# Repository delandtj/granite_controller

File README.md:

# granite

The Granite immersion frame electronics: the 48 V power plane, the
plane-core firmware, the controller and the software shared between them.

granite_controller and granite-plane merged on 2026-10-30. granite-plane
was split from granite_controller on 2026-10-29; its commits were replayed
on top of granite_controller's history, so both histories are here.

## Layout

- controller-fd: the controller with the CAN FD plane link (ADR 0006),
  the live design. tools/fd_build.sh builds it from the rev D board in
  attic/controller-rev-d.
- controller-rev-c: the rev C controller board (relays, expanders, 19 V
  input), kept as demoware. Tag rev-c-demo is the last rev C state of
  the whole repo, firmware included.
- power/pp-48-fd: plane tools and libraries for the CAN FD link
  (ADR 0006). power/pp-48-core-fd, power/pp-48-unit-fd: the chained plane
  (ADR 0005), one core board and identical 2-slot unit boards.
- power/pp-48: the I2C-link plane tools (schematic generator, placement
  and routing scripts), pp.kicad_sym, pp48.pretty, pp48.3dshapes; its
  schematic engine is also used by pm-19v-250w-b, and the attic boards
  use its libraries.
- power/pm-19v-250w, power/pm-19v-250w-b: the port module. power/pm-bench-carrier: bench
  carrier for one module. power/tools: module mount geometry.
- mech: the mechanical side. mech/frame: the 3D-printed pod frames
  (node, infra and end frame, plane carrier), FreeCAD models and
  freecadcmd generators; mech/pod-layout: the pod layout page;
  mech/halo-clamp: the Strix Halo cooler bridge; mech/assembly: the
  8-port plane assembly. Handoff in docs/handoff-frames.md. Moved in
  from ~/Granite/Hardware on 2026-11-26.
- site: installer / operator manual (mdBook). Still describes rev C
  (relays, expanders, 19 V input); to be reworked for rev D and the plane.
- firmware: Rust workspace. granite-core (no_std: dispatcher, commands,
  MQTT / HTTP / Modbus surfaces, rules, config), granite-sim (host
  simulator), granite-fw (ESP32-C6 binary, still the rev C hardware
  layer), web UI.
- docs: ADRs 0001-0007, plane requirements, module interface, controller
  specs, handoff. Firmware ADRs in firmware/docs/adr.
- attic: superseded designs, kept for reference, not maintained.
  - attic/power/pp-48-2s: the first 2-slot plane (ADR 0001 / 0002).
  - attic/power/pm-19v-200w: the first port module (obsolete since
    2026-10-27, replaced by pm-19v-250w).
  - attic/power/pp-48-rev1: the single-board plane (ADR 0004, tag
    pp48-rev1); uses the libraries in power/pp-48.
  - attic/controller-rev-d: the I2C-link controller (rev D), superseded
    by controller-fd (2026-11-10); still the input board of
    controller-fd/tools/fd_build.sh.
  - attic/power/pp-48-core, attic/power/pp-48-unit: the I2C-link chained
    plane (ADR 0005), superseded by the -fd boards (2026-11-10); still the
    input boards of power/pp-48-fd/tools/fd_layout.sh and the output of
    power/pp-48/tools/gensch.py.
  - attic/firmware/plane-fw, attic/firmware/plane-core-pins.toml: the
    rev D plane binary (I2C link) and its pin map, frozen 2026-11-10;
    builds against firmware/granite-proto and firmware/plane-logic. The
    FD plane binary is firmware/plane-fd (firmware ADR 0005 decision 9).
  Older docs and the handoff name these at their old paths
  (power/pp-48-2s, power/pm-19v-200w, power/pp-48/pp-48.kicad_*,
  controller, power/pp-48-core, power/pp-48-unit).

## Direction (decided 2026-10-29)

- Plane core firmware on the STM32G070 (embassy), I2C slave to the
  controller, master to the units through the TCA9548A.
- Plane firmware updated from the controller over the link: own A/B
  bootloader (embassy-boot) that keeps the plane's strapped address,
  rollback on a failed self-test. ST's ROM bootloader only as a bench
  recovery path.
- The plane core owns node sequencing (press deadlines, power-cycle,
  retry / latch policy, stagger); the controller does policy, rules and
  the network.
- One controller serves several planes over isolated I2C (ISO1640 +
  EXP_INT, daisy chain, plane addresses 0x30-0x37).
- One TLV protocol crate used by the plane firmware, the controller and
  the simulator.
- Controller rev D: rev C minus the relays, expanders, LED sense and
  19 V input; 12 V from the plane's isolated aux.

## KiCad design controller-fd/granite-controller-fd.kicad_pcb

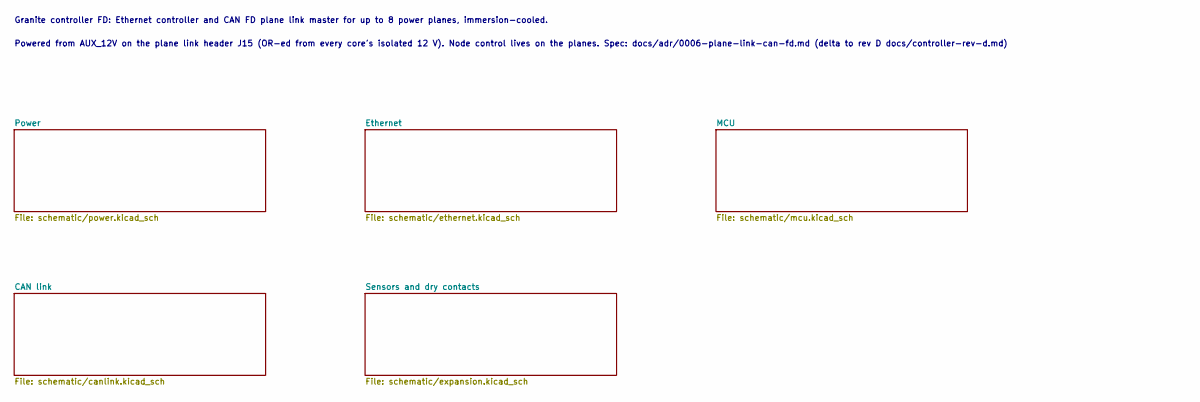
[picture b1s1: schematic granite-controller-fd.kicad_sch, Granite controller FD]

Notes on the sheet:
Granite controller FD: Ethernet controller and CAN FD plane link master for up to 8 power planes, immersion-cooled.
Powered from AUX_12V on the plane link header J15 (OR-ed from every core's isolated 12 V). Node control lives on the planes. Spec: docs/adr/0006-plane-link-can-fd.md (delta to rev D docs/controller-rev-d.md)

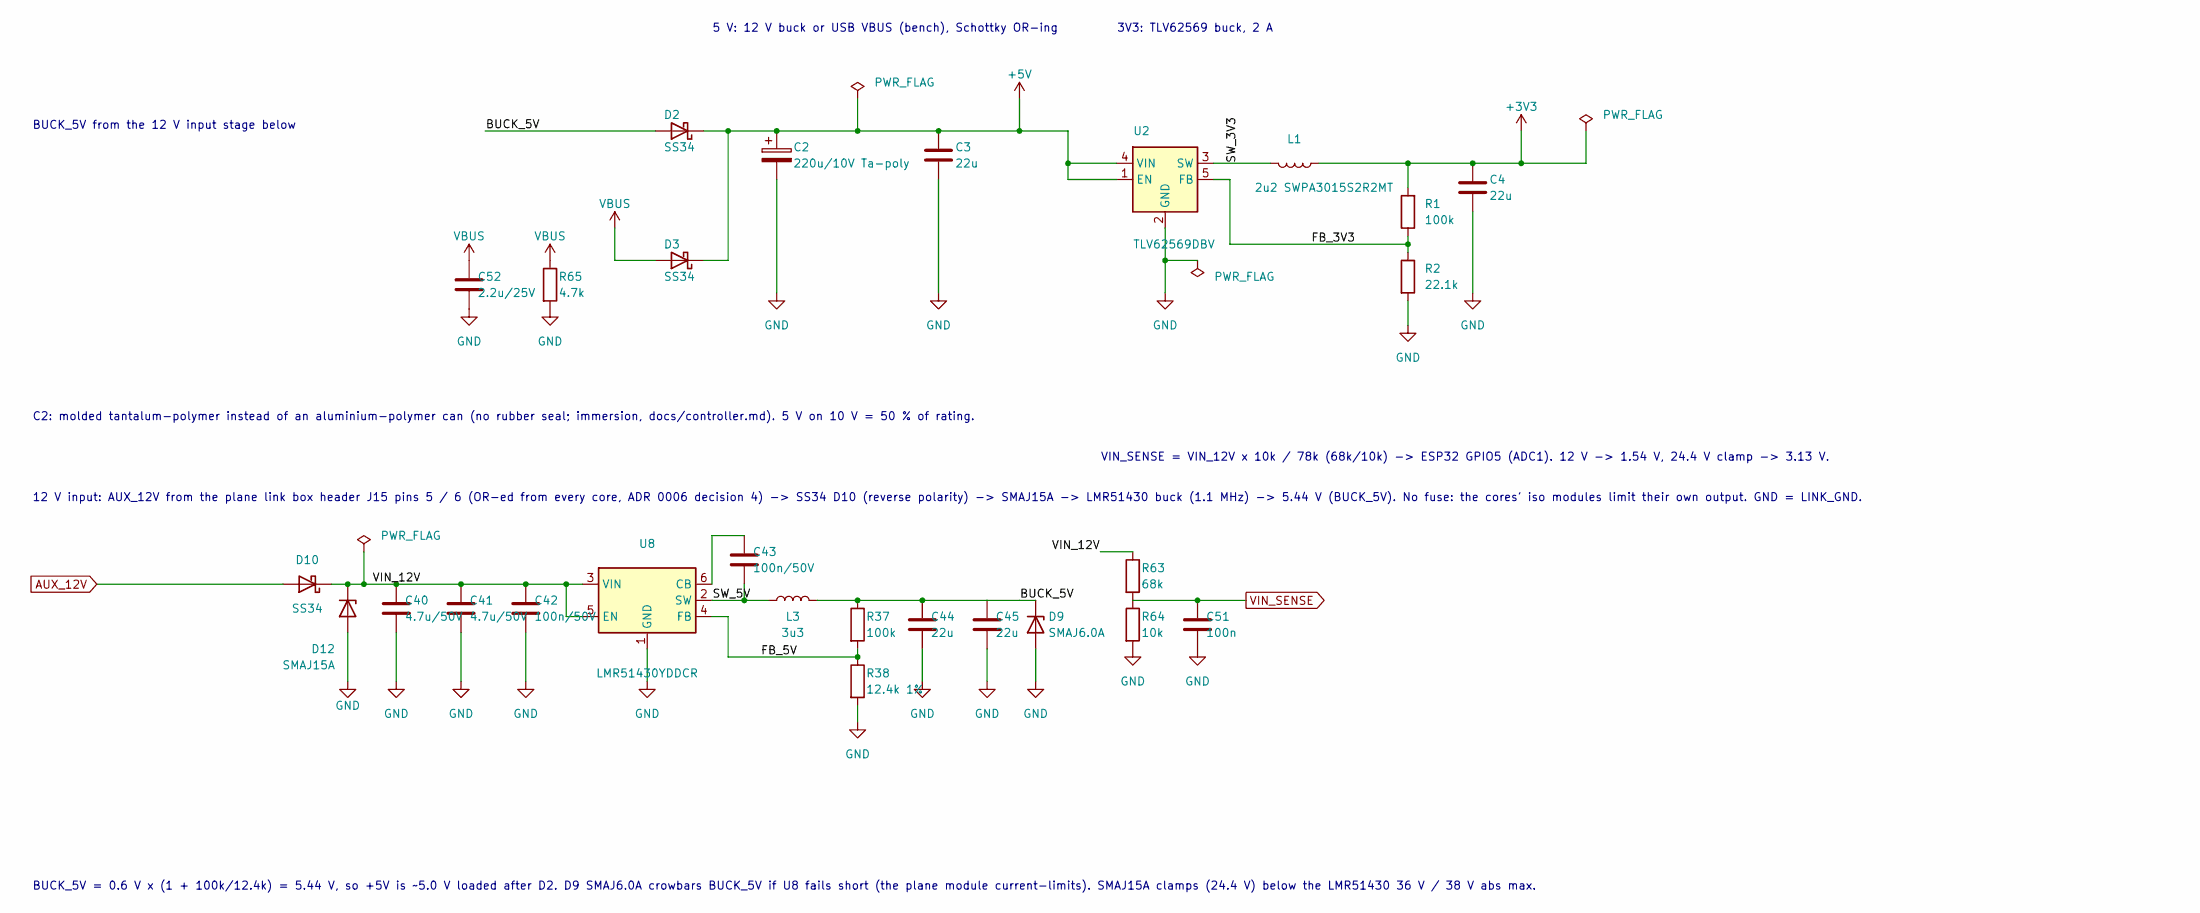
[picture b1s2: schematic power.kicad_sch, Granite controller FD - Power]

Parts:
C2: 220u/10V Ta-poly; CP_EIA-7343-31_Kemet-D; MPN T520D227M010ATE018; LCSC C116742
C3, C4, C44, C45: 22u; C_0805_2012Metric; MPN CL21A226MAQNNNE; LCSC C45783
C40, C41: 4.7u/50V; C_1206_3216Metric; MPN 1206B475K500NT; LCSC C29823
C42, C43: 100n/50V; C_0402_1005Metric; MPN CL05B104KB54PNC; LCSC C307331
C51: 100n; C_0402_1005Metric; MPN CL05B104KO5NNNC; LCSC C1525
C52: 2.2u/25V; C_0603_1608Metric; MPN CL10A225KA8NNNC; LCSC C57895
D2, D3, D10: SS34; D_SMA; MPN SS34; LCSC C8678
D9: SMAJ6.0A; D_SMA; MPN SMAJ6.0A; LCSC C364284
D12: SMAJ15A; D_SMA; MPN SMAJ15A; LCSC C148216
L1: 2u2 SWPA3015S2R2MT; L_Sunlord_SWPA3015S; MPN SWPA3015S2R2MT; LCSC C43389
L3: 3u3; L_Changjiang_FXL0630; MPN FXL0630-3R3-M; LCSC C167219
R1, R37: 100k; R_0402_1005Metric; MPN 0402WGF1003TCE; LCSC C25741
R2: 22.1k; R_0402_1005Metric; MPN RC0402FR-0722K1L; LCSC C163478
R38: 12.4k 1%; R_0402_1005Metric; MPN 0402WGF1242TCE; LCSC C11692
R63: 68k; R_0402_1005Metric; MPN 0402WGF6802TCE; LCSC C36871
R64: 10k; R_0402_1005Metric; MPN 0402WGF1002TCE; LCSC C25744
R65: 4.7k; R_0402_1005Metric; MPN 0402WGF4701TCE; LCSC C25900
U2: TLV62569DBV; SOT-23-5; MPN TLV62569DBVR; LCSC C141836
U8: LMR51430YDDCR; SOT-23-6; MPN LMR51430YDDCR; LCSC C5210749

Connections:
+3V3: C4.1, L1.1, R1.2; also elsewhere on the board
+5V: C2.1, C3.1, D2.1 (K), D3.1 (K), U2.1 (EN), U2.4 (VIN); also elsewhere on the board
/Power/BUCK_5V: C44.1, C45.1, D2.2 (A), D9.1 (K), L3.2, R37.1
/Power/FB_3V3: R1.1, R2.1, U2.5 (FB)
/Power/FB_5V: R37.2, R38.1, U8.4 (FB)
/Power/SW_3V3: L1.2, U2.3 (SW)
/Power/SW_5V: C43.2, L3.1, U8.2 (SW)
/Power/VIN_12V: C40.1, C41.1, C42.1, D10.1 (K), D12.1 (K), R63.1, U8.3 (VIN), U8.5 (EN)
AUX_12V: D10.2 (A); also elsewhere on the board
GND: C2.2, C3.2, C4.2, C40.2, C41.2, C42.2, C44.2, C45.2, C51.2, C52.2, D9.2 (A), D12.2 (A), R2.2, R38.2, R64.2, R65.2, U2.2 (GND), U8.1 (GND); also elsewhere on the board
unnamed: C43.1, U8.6 (CB)
VBUS: C52.1, D3.2 (A), R65.1; also elsewhere on the board
VIN_SENSE: C51.1, R63.2, R64.1; also elsewhere on the board

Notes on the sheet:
5 V: 12 V buck or USB VBUS (bench), Schottky OR-ing
3V3: TLV62569 buck, 2 A
BUCK_5V from the 12 V input stage below
12 V input: AUX_12V from the plane link box header J15 pins 5 / 6 (OR-ed from every core, ADR 0006 decision 4) -> SS34 D10 (reverse polarity) -> SMAJ15A -> LMR51430 buck (1.1 MHz) -> 5.44 V (BUCK_5V). No fuse: the cores' iso modules limit their own output. GND = LINK_GND.
BUCK_5V = 0.6 V x (1 + 100k/12.4k) = 5.44 V, so +5V is ~5.0 V loaded after D2. D9 SMAJ6.0A crowbars BUCK_5V if U8 fails short (the plane module current-limits). SMAJ15A clamps (24.4 V) below the LMR51430 36 V / 38 V abs max.
C2: molded tantalum-polymer instead of an aluminium-polymer can (no rubber seal; immersion, docs/controller.md). 5 V on 10 V = 50 % of rating.
VIN_SENSE = VIN_12V x 10k / 78k (68k/10k) -> ESP32 GPIO5 (ADC1). 12 V -> 1.54 V, 24.4 V clamp -> 3.13 V.

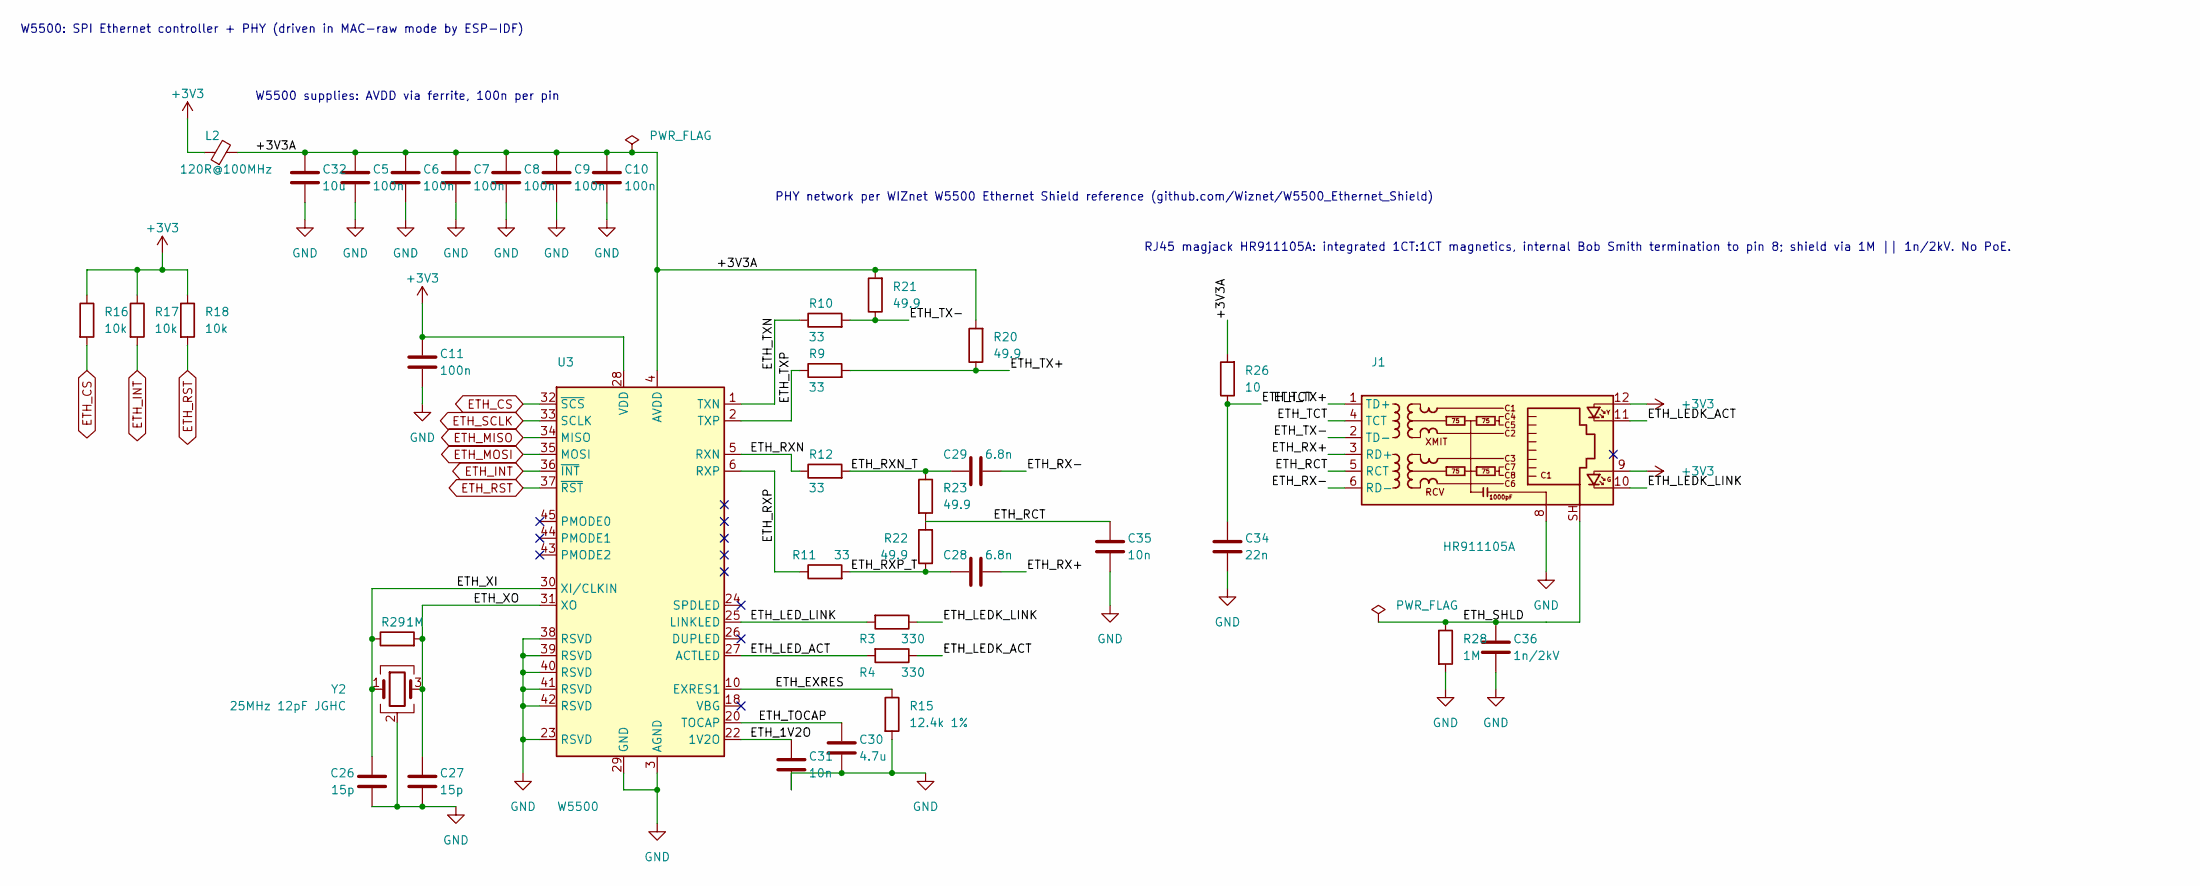
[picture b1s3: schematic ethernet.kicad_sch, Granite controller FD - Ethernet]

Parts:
C5, C6, C7, C8, C9, C10, C11: 100n; C_0402_1005Metric; MPN CL05B104KO5NNNC; LCSC C1525
C26, C27: 15p; C_0402_1005Metric; MPN 0402CG150J500NT; LCSC C1548
C28, C29: 6.8n; C_0402_1005Metric; MPN CC0402KRX7R9BB682; LCSC C93654
C30: 4.7u; C_0603_1608Metric; MPN CL10A475KO8NNNC; LCSC C19666
C31, C35: 10n; C_0402_1005Metric; MPN CL05B103KB5NNNC; LCSC C15195
C32: 10u; C_0805_2012Metric; MPN CL21A106KAYNNNE; LCSC C15850
C34: 22n; C_0402_1005Metric; MPN 0402B223K500NT; LCSC C1532
C36: 1n/2kV; C_1812_4532Metric; MPN CC1812KKX7RDBB102; LCSC C118019
J1: HR911105A; RJ45_Hanrun_HR911105A_Horizontal; MPN HR911105A; LCSC C12074
L2: 120R@100MHz; L_0603_1608Metric; MPN BLM18PG121SN1D; LCSC C14709
R3, R4: 330; R_0402_1005Metric; MPN 0402WGF3300TCE; LCSC C25104
R9, R10, R11, R12: 33; R_0402_1005Metric; MPN 0402WGF330JTCE; LCSC C25105
R15: 12.4k 1%; R_0402_1005Metric; MPN 0402WGF1242TCE; LCSC C11692
R16, R17, R18: 10k; R_0402_1005Metric; MPN 0402WGF1002TCE; LCSC C25744
R20, R21, R22, R23: 49.9; R_0402_1005Metric; MPN 0402WGF499JTCE; LCSC C25120
R26: 10; R_0402_1005Metric; MPN 0402WGF100JTCE; LCSC C25077
R28: 1M; R_0603_1608Metric; MPN 0603WAF1004T5E; LCSC C22935
R29: 1M; R_0402_1005Metric; MPN 0402WGF1004TCE; LCSC C26083
U3: W5500; LQFP-48_7x7mm_P0.5mm; MPN W5500; LCSC C32843
Y2: 25MHz 12pF JGHC; Crystal_SMD_Abracon_ABM8G-4Pin_3.2x2.5mm; MPN S3225000121060; LCSC C390773

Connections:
+3V3: C11.1, J1.9, J1.12, L2.1, R16.1, R17.1, R18.1, U3.28 (VDD); also elsewhere on the board
/Ethernet/+3V3A: C5.1, C6.1, C7.1, C8.1, C9.1, C10.1, C32.1, L2.2, R20.2, R21.2, R26.2, U3.4 (AVDD), U3.8 (AVDD), U3.11 (AVDD), U3.15 (AVDD), U3.17 (AVDD), U3.21 (AVDD)
/Ethernet/ETH_1V2O: C31.1, U3.22 (1V2O)
/Ethernet/ETH_EXRES: R15.1, U3.10 (EXRES1)
/Ethernet/ETH_LEDK_ACT: J1.11, R4.1
/Ethernet/ETH_LEDK_LINK: J1.10, R3.1
/Ethernet/ETH_LED_ACT: R4.2, U3.27 (ACTLED)
/Ethernet/ETH_LED_LINK: R3.2, U3.25 (LINKLED)
/Ethernet/ETH_RCT: C35.1, J1.5 (RCT), R22.2, R23.2
/Ethernet/ETH_RX+: C28.2, J1.3 (RD+)
/Ethernet/ETH_RX-: C29.2, J1.6 (RD-)
/Ethernet/ETH_RXN: R12.1, U3.5 (RXN)
/Ethernet/ETH_RXN_T: C29.1, R12.2, R23.1
/Ethernet/ETH_RXP: R11.1, U3.6 (RXP)
/Ethernet/ETH_RXP_T: C28.1, R11.2, R22.1
/Ethernet/ETH_SHLD: C36.1, J1.SH, R28.1
/Ethernet/ETH_TCT: C34.1, J1.4 (TCT), R26.1
/Ethernet/ETH_TOCAP: C30.1, U3.20 (TOCAP)
/Ethernet/ETH_TX+: J1.1 (TD+), R9.2, R20.1
/Ethernet/ETH_TX-: J1.2 (TD-), R10.2, R21.1
/Ethernet/ETH_TXN: R10.1, U3.1 (TXN)
/Ethernet/ETH_TXP: R9.1, U3.2 (TXP)
/Ethernet/ETH_XI: C26.1, R29.1, U3.30 (XI/CLKIN), Y2.1
/Ethernet/ETH_XO: C27.1, R29.2, U3.31 (XO), Y2.3
ETH_CS: R16.2, U3.32 (~SCS); also elsewhere on the board
ETH_INT: R17.2, U3.36 (~INT); also elsewhere on the board
ETH_MISO: U3.34 (MISO); also elsewhere on the board
ETH_MOSI: U3.35 (MOSI); also elsewhere on the board
ETH_RST: R18.2, U3.37 (~RST); also elsewhere on the board
ETH_SCLK: U3.33 (SCLK); also elsewhere on the board
GND: C5.2, C6.2, C7.2, C8.2, C9.2, C10.2, C11.2, C26.2, C27.2, C30.2, C31.2, C32.2, C34.2, C35.2, C36.2, J1.8, R15.2, R28.2, U3.3 (AGND), U3.9 (AGND), U3.14 (AGND), U3.16 (AGND), U3.19 (AGND), U3.23 (RSVD), U3.29 (GND), U3.38 (RSVD), U3.39 (RSVD), U3.40 (RSVD), U3.41 (RSVD), U3.42 (RSVD), U3.48 (AGND), Y2.2 (G), Y2.4 (G); also elsewhere on the board

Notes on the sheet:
W5500: SPI Ethernet controller + PHY (driven in MAC-raw mode by ESP-IDF)
W5500 supplies: AVDD via ferrite, 100n per pin
PHY network per WIZnet W5500 Ethernet Shield reference (github.com/Wiznet/W5500_Ethernet_Shield)
RJ45 magjack HR911105A: integrated 1CT:1CT magnetics, internal Bob Smith termination to pin 8; shield via 1M || 1n/2kV. No PoE.

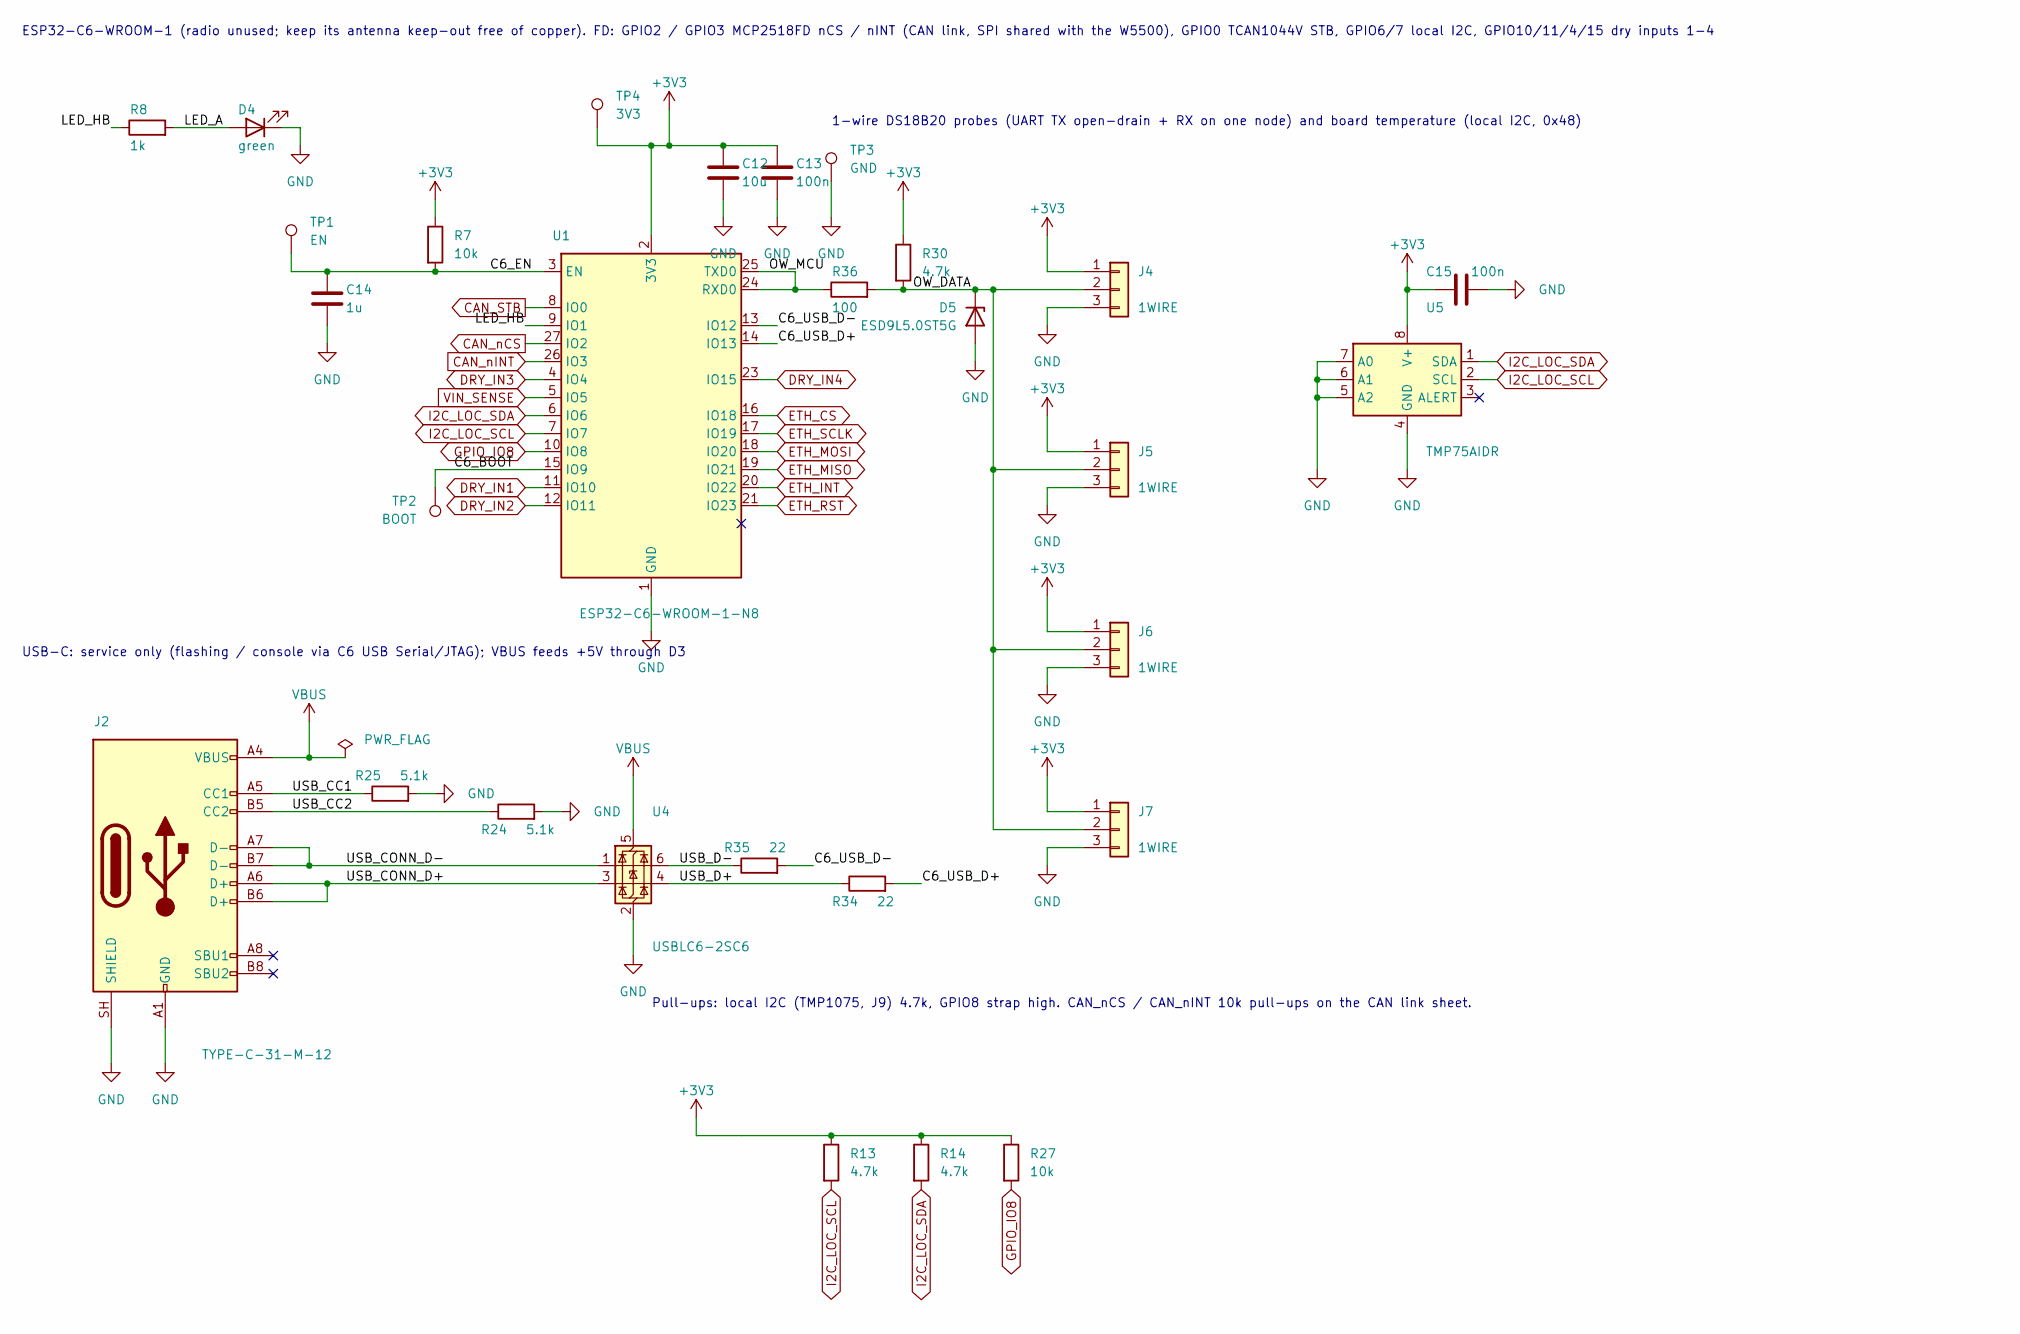
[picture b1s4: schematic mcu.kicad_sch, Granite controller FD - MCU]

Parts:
C12: 10u; C_0805_2012Metric; MPN CL21A106KAYNNNE; LCSC C15850
C13, C15: 100n; C_0402_1005Metric; MPN CL05B104KO5NNNC; LCSC C1525
C14: 1u; C_0603_1608Metric; MPN CL10A105KB8NNNC; LCSC C15849
D4: green; LED_0603_1608Metric; MPN KT-0603G; LCSC C12624
D5: ESD9L5.0ST5G; D_SOD-923; MPN ESD9L5.0ST5G; LCSC C82326
J2: TYPE-C-31-M-12; USB_C_Receptacle_HRO_TYPE-C-31-M-12; MPN TYPE-C-31-M-12; LCSC C165948
J4, J5, J6, J7: 1WIRE; JST_PH_B3B-PH-K_1x03_P2.00mm_Vertical; MPN B3B-PH-K-S(LF)(SN); LCSC C131339
R7, R27: 10k; R_0402_1005Metric; MPN 0402WGF1002TCE; LCSC C25744
R8: 1k; R_0402_1005Metric; MPN 0402WGF1001TCE; LCSC C11702
R13, R14, R30: 4.7k; R_0402_1005Metric; MPN 0402WGF4701TCE; LCSC C25900
R24, R25: 5.1k; R_0402_1005Metric; MPN 0402WGF5101TCE; LCSC C25905
R34, R35: 22; R_0402_1005Metric; MPN 0402WGF220JTCE; LCSC C25092
R36: 100; R_0603_1608Metric; MPN 0603WAF1000T5E; LCSC C22775
TP1: EN; TestPoint_Pad_D1.5mm
TP2: BOOT; TestPoint_Pad_D1.5mm
TP3: GND; TestPoint_Pad_D1.5mm
TP4: 3V3; TestPoint_Pad_D1.5mm
U1: ESP32-C6-WROOM-1-N8; ESP32-C6-WROOM-1; MPN ESP32-C6-WROOM-1-N8; LCSC C5366877
U4: USBLC6-2SC6; SOT-23-6; MPN USBLC6-2SC6; LCSC C7519
U5: TMP75AIDR; SOIC-8_3.9x4.9mm_P1.27mm; MPN TMP75AIDR; LCSC C30389

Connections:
+3V3: C12.1, C13.1, C15.1, J4.1, J5.1, J6.1, J7.1, R7.1, R13.1, R14.1, R27.1, R30.1, TP4.1, U1.2 (3V3), U5.8 (V+); also elsewhere on the board
/MCU/C6_BOOT: TP2.1, U1.15 (IO9)
/MCU/C6_EN: C14.1, R7.2, TP1.1, U1.3 (EN)
/MCU/C6_USB_D+: R34.2, U1.14 (IO13)
/MCU/C6_USB_D-: R35.2, U1.13 (IO12)
/MCU/LED_A: D4.2 (A), R8.2
/MCU/LED_HB: R8.1, U1.9 (IO1)
/MCU/OW_DATA: D5.1 (K), J4.2, J5.2, J6.2, J7.2, R30.2, R36.2
/MCU/OW_MCU: R36.1, U1.24 (RXD0), U1.25 (TXD0)
/MCU/USB_CC1: J2.A5 (CC1), R25.1
/MCU/USB_CC2: J2.B5 (CC2), R24.1
/MCU/USB_CONN_D+: J2.A6 (D+), J2.B6 (D+), U4.3 (I/O2)
/MCU/USB_CONN_D-: J2.A7 (D-), J2.B7 (D-), U4.1 (I/O1)
/MCU/USB_D+: R34.1, U4.4 (I/O2)
/MCU/USB_D-: R35.1, U4.6 (I/O1)
CAN_STB: U1.8 (IO0); also elsewhere on the board
CAN_nCS: U1.27 (IO2); also elsewhere on the board
CAN_nINT: U1.26 (IO3); also elsewhere on the board
DRY_IN1: U1.11 (IO10); also elsewhere on the board
DRY_IN2: U1.12 (IO11); also elsewhere on the board
DRY_IN3: U1.4 (IO4); also elsewhere on the board
DRY_IN4: U1.23 (IO15); also elsewhere on the board
ETH_CS: U1.16 (IO18); also elsewhere on the board
ETH_INT: U1.20 (IO22); also elsewhere on the board
ETH_MISO: U1.19 (IO21); also elsewhere on the board
ETH_MOSI: U1.18 (IO20); also elsewhere on the board
ETH_RST: U1.21 (IO23); also elsewhere on the board
ETH_SCLK: U1.17 (IO19); also elsewhere on the board
GND: C12.2, C13.2, C14.2, C15.2, D4.1 (K), D5.2 (A), J2.A1 (GND), J2.A12 (GND), J2.B1 (GND), J2.B12 (GND), J2.SH (SHIELD), J4.3, J5.3, J6.3, J7.3, R24.2, R25.2, TP3.1, U1.1 (GND), U1.28 (GND), U1.29 (GND), U4.2 (GND), U5.4 (GND), U5.5 (A2), U5.6 (A1), U5.7 (A0); also elsewhere on the board
GPIO_IO8: R27.2, U1.10 (IO8)
I2C_LOC_SCL: R13.2, U1.7 (IO7), U5.2 (SCL); also elsewhere on the board
I2C_LOC_SDA: R14.2, U1.6 (IO6), U5.1 (SDA); also elsewhere on the board
VBUS: J2.A4 (VBUS), J2.A9 (VBUS), J2.B4 (VBUS), J2.B9 (VBUS), U4.5 (VBUS); also elsewhere on the board
VIN_SENSE: U1.5 (IO5); also elsewhere on the board

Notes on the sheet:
ESP32-C6-WROOM-1 (radio unused; keep its antenna keep-out free of copper). FD: GPIO2 / GPIO3 MCP2518FD nCS / nINT (CAN link, SPI shared with the W5500), GPIO0 TCAN1044V STB, GPIO6/7 local I2C, GPIO10/11/4/15 dry inputs 1-4
1-wire DS18B20 probes (UART TX open-drain + RX on one node) and board temperature (local I2C, 0x48)
USB-C: service only (flashing / console via C6 USB Serial/JTAG); VBUS feeds +5V through D3
Pull-ups: local I2C (TMP1075, J9) 4.7k, GPIO8 strap high. CAN_nCS / CAN_nINT 10k pull-ups on the CAN link sheet.

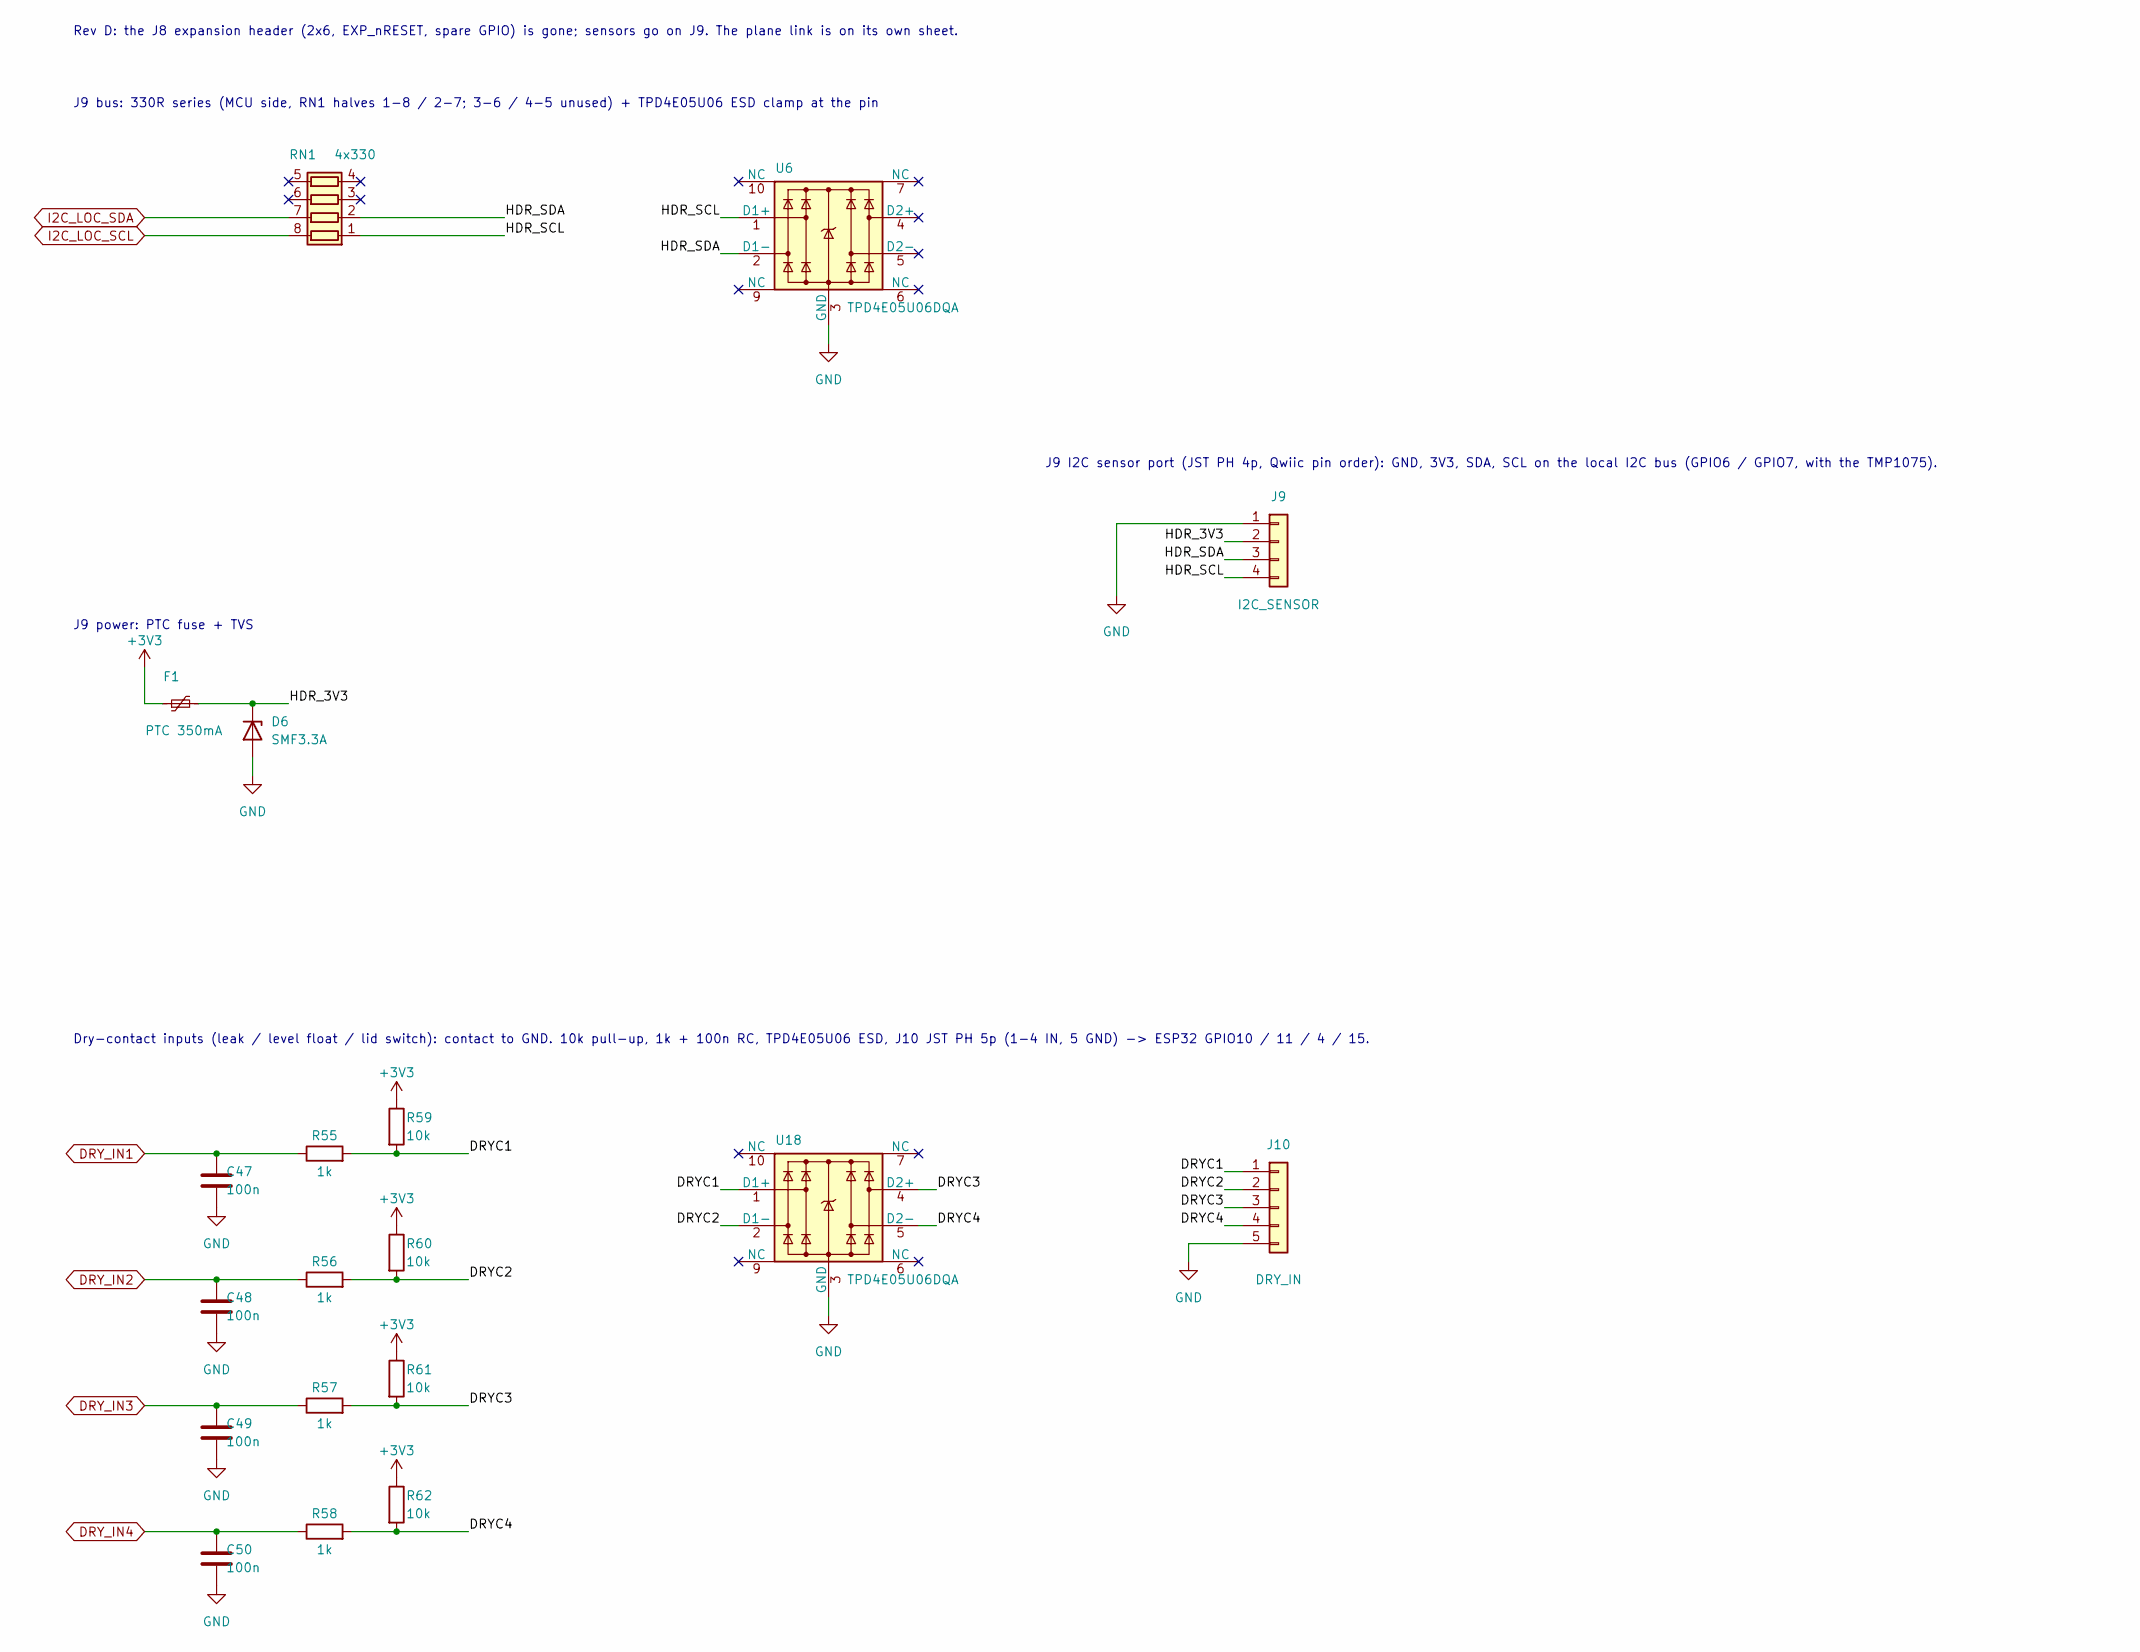
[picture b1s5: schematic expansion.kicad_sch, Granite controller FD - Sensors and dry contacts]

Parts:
C47, C48, C49, C50: 100n; C_0402_1005Metric; MPN CL05B104KO5NNNC; LCSC C1525
D6: SMF3.3A; D_SOD-123F; MPN SMF3.3A; LCSC C37331473
F1: PTC 350mA; Fuse_0805_2012Metric; MPN 0805L035/24XR; LCSC C7472565
J9: I2C_SENSOR; JST_PH_B4B-PH-K_1x04_P2.00mm_Vertical; MPN B4B-PH-K-S(LF)(SN); LCSC C131334
J10: DRY_IN; JST_PH_B5B-PH-K_1x05_P2.00mm_Vertical; MPN B5B-PH-K-S(LF)(SN); LCSC C157993
R55, R56, R57, R58: 1k; R_0402_1005Metric; MPN 0402WGF1001TCE; LCSC C11702
R59, R60, R61, R62: 10k; R_0402_1005Metric; MPN 0402WGF1002TCE; LCSC C25744
RN1: 4x330; R_Array_Convex_4x0402; MPN 4D02WGJ0331TCE; LCSC C43557
U6, U18: TPD4E05U06DQA; USON-10_2.5x1.0mm_P0.5mm; MPN TPD4E05U06DQAR; LCSC C138714

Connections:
+3V3: F1.1, R59.1, R60.1, R61.1, R62.1; also elsewhere on the board
/Sensors and dry contacts/DRYC1: J10.1, R55.2, R59.2, U18.1 (D1+)
/Sensors and dry contacts/DRYC2: J10.2, R56.2, R60.2, U18.2 (D1-)
/Sensors and dry contacts/DRYC3: J10.3, R57.2, R61.2, U18.4 (D2+)
/Sensors and dry contacts/DRYC4: J10.4, R58.2, R62.2, U18.5 (D2-)
/Sensors and dry contacts/HDR_3V3: D6.1 (K), F1.2, J9.2
/Sensors and dry contacts/HDR_SCL: J9.4, RN1.1 (R1.1), U6.1 (D1+)
/Sensors and dry contacts/HDR_SDA: J9.3, RN1.2 (R2.1), U6.2 (D1-)
DRY_IN1: C47.1, R55.1; also elsewhere on the board
DRY_IN2: C48.1, R56.1; also elsewhere on the board
DRY_IN3: C49.1, R57.1; also elsewhere on the board
DRY_IN4: C50.1, R58.1; also elsewhere on the board
GND: C47.2, C48.2, C49.2, C50.2, D6.2 (A), J9.1, J10.5, U6.3 (GND), U6.8 (GND), U18.3 (GND), U18.8 (GND); also elsewhere on the board
I2C_LOC_SCL: RN1.8 (R1.2); also elsewhere on the board
I2C_LOC_SDA: RN1.7 (R2.2); also elsewhere on the board

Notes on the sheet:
Rev D: the J8 expansion header (2x6, EXP_nRESET, spare GPIO) is gone; sensors go on J9. The plane link is on its own sheet.
J9 bus: 330R series (MCU side, RN1 halves 1-8 / 2-7; 3-6 / 4-5 unused) + TPD4E05U06 ESD clamp at the pin
J9 power: PTC fuse + TVS
J9 I2C sensor port (JST PH 4p, Qwiic pin order): GND, 3V3, SDA, SCL on the local I2C bus (GPIO6 / GPIO7, with the TMP1075).
Dry-contact inputs (leak / level float / lid switch): contact to GND. 10k pull-up, 1k + 100n RC, TPD4E05U06 ESD, J10 JST PH 5p (1-4 IN, 5 GND) -> ESP32 GPIO10 / 11 / 4 / 15.

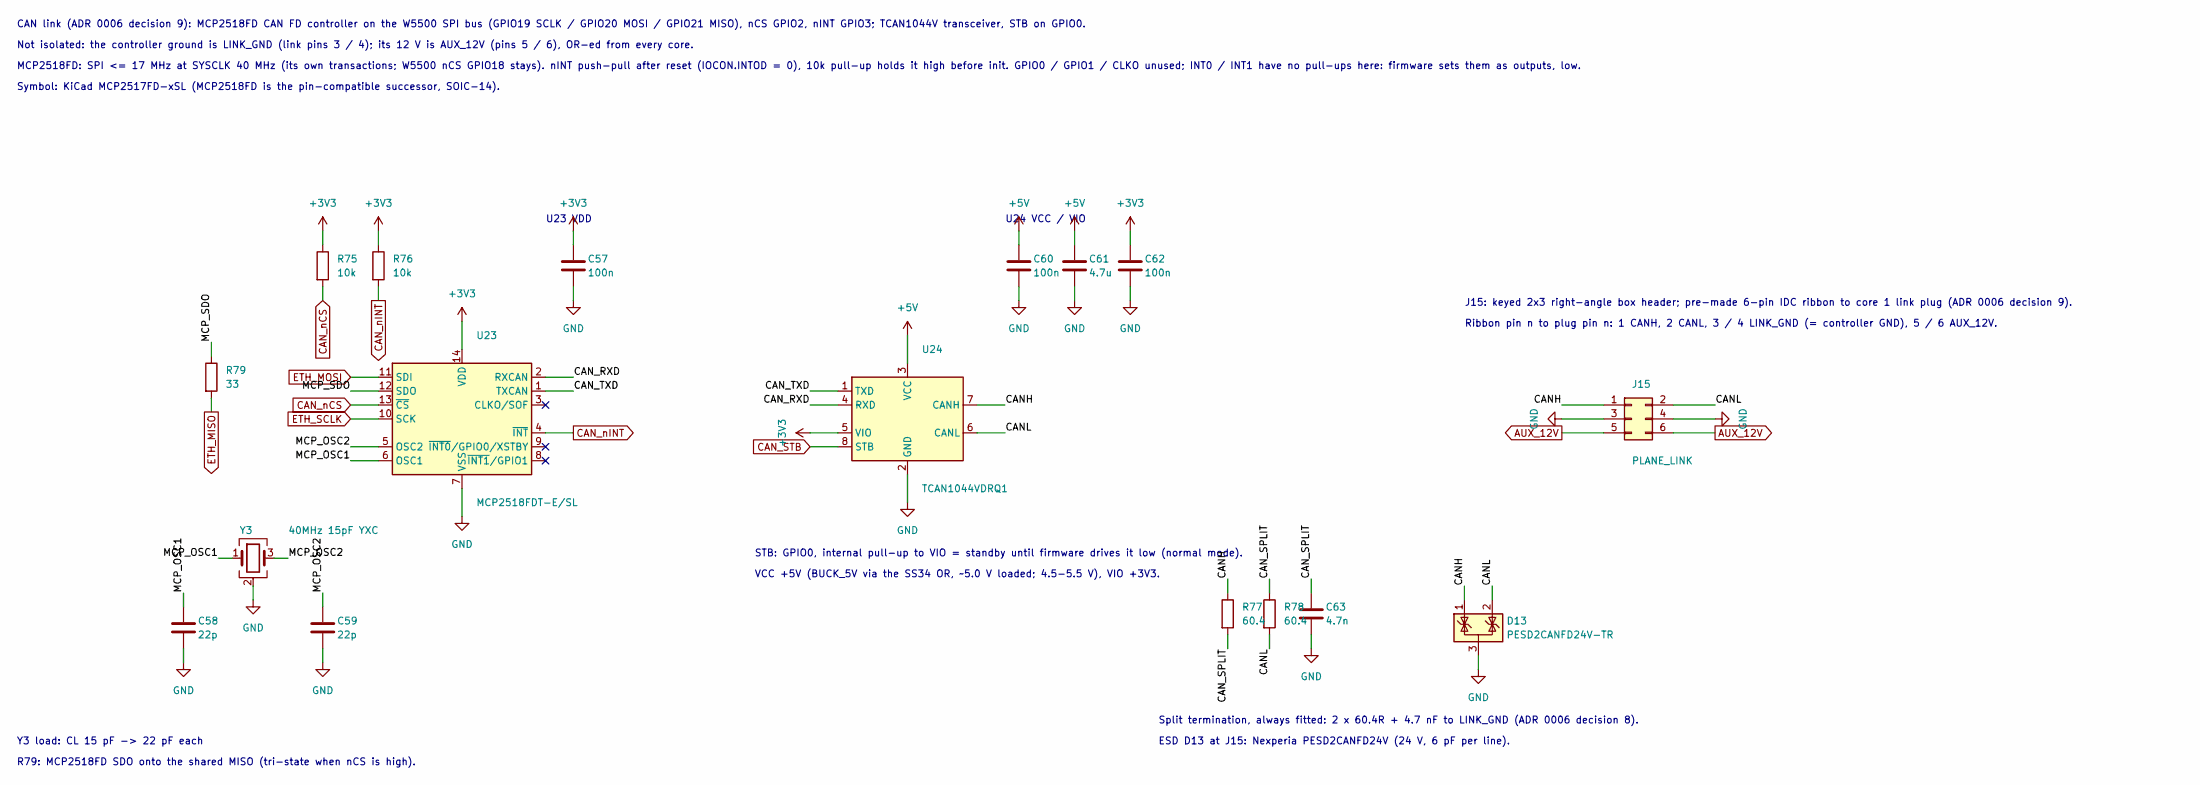
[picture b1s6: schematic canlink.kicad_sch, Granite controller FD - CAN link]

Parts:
C57, C60, C62: 100n; C_0402_1005Metric; MPN CL05B104KO5NNNC; LCSC C1525
C58, C59: 22p; C_0402_1005Metric; MPN 0402CG220J500NT; LCSC C1555
C61: 4.7u; C_0603_1608Metric; MPN CL10A475KO8NNNC; LCSC C19666
C63: 4.7n; C_0402_1005Metric; MPN 0402B472K500NT; LCSC C1538
D13: PESD2CANFD24V-TR; SOT-23; MPN PESD2CANFD24V-TR; LCSC C552486
J15: PLANE_LINK; IDC-Header_2x03_P2.54mm_Horizontal; MPN 2.54-2*3P Bent Header; LCSC C34945
R75, R76: 10k; R_0402_1005Metric; MPN 0402WGF1002TCE; LCSC C25744
R77, R78: 60.4; R_0402_1005Metric; MPN 0402WGF604JTCE; LCSC C60310
R79: 33; R_0402_1005Metric; MPN 0402WGF330JTCE; LCSC C25105
U23: MCP2518FDT-E/SL; SOIC-14_3.9x8.7mm_P1.27mm; MPN MCP2518FDT-E/SL; LCSC C626758
U24: TCAN1044VDRQ1; SOIC-8_3.9x4.9mm_P1.27mm; MPN TCAN1044VDRQ1; LCSC C1852061
Y3: 40MHz 15pF YXC; Crystal_SMD_Abracon_ABM8G-4Pin_3.2x2.5mm; MPN X322540MPB4SI; LCSC C9010

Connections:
+3V3: C57.1, C62.1, R75.1, R76.1, U23.14 (VDD), U24.5 (VIO); also elsewhere on the board
+5V: C60.1, C61.1, U24.3 (VCC); also elsewhere on the board
/CAN link/CANH: D13.1 (K), J15.1, R77.1, U24.7 (CANH)
/CAN link/CANL: D13.2 (K), J15.2, R78.2, U24.6 (CANL)
/CAN link/CAN_RXD: U23.2 (RXCAN), U24.4 (RXD)
/CAN link/CAN_SPLIT: C63.1, R77.2, R78.1
/CAN link/CAN_TXD: U23.1 (TXCAN), U24.1 (TXD)
/CAN link/MCP_OSC1: C58.1, U23.6 (OSC1), Y3.1
/CAN link/MCP_OSC2: C59.1, U23.5 (OSC2), Y3.3
/CAN link/MCP_SDO: R79.1, U23.12 (SDO)
AUX_12V: J15.5, J15.6; also elsewhere on the board
CAN_STB: U24.8 (STB); also elsewhere on the board
CAN_nCS: R75.2, U23.13 (~CS); also elsewhere on the board
CAN_nINT: R76.2, U23.4 (~INT); also elsewhere on the board
ETH_MISO: R79.2; also elsewhere on the board
ETH_MOSI: U23.11 (SDI); also elsewhere on the board
ETH_SCLK: U23.10 (SCK); also elsewhere on the board
GND: C57.2, C58.2, C59.2, C60.2, C61.2, C62.2, C63.2, D13.3 (A), J15.3, J15.4, U23.7 (VSS), U24.2 (GND), Y3.2 (G), Y3.4 (G); also elsewhere on the board

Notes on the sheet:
CAN link (ADR 0006 decision 9): MCP2518FD CAN FD controller on the W5500 SPI bus (GPIO19 SCLK / GPIO20 MOSI / GPIO21 MISO), nCS GPIO2, nINT GPIO3; TCAN1044V transceiver, STB on GPIO0.
Not isolated: the controller ground is LINK_GND (link pins 3 / 4); its 12 V is AUX_12V (pins 5 / 6), OR-ed from every core.
MCP2518FD: SPI <= 17 MHz at SYSCLK 40 MHz (its own transactions; W5500 nCS GPIO18 stays). nINT push-pull after reset (IOCON.INTOD = 0), 10k pull-up holds it high before init. GPIO0 / GPIO1 / CLKO unused; INT0 / INT1 have no pull-ups here: firmware sets them as outputs, low.
Symbol: KiCad MCP2517FD-xSL (MCP2518FD is the pin-compatible successor, SOIC-14).
R79: MCP2518FD SDO onto the shared MISO (tri-state when nCS is high).
U23 VDD
Y3 load: CL 15 pF -> 22 pF each
STB: GPIO0, internal pull-up to VIO = standby until firmware drives it low (normal mode).
VCC +5V (BUCK_5V via the SS34 OR, ~5.0 V loaded; 4.5-5.5 V), VIO +3V3.
U24 VCC / VIO
J15: keyed 2x3 right-angle box header; pre-made 6-pin IDC ribbon to core 1 link plug (ADR 0006 decision 9).
Ribbon pin n to plug pin n: 1 CANH, 2 CANL, 3 / 4 LINK_GND (= controller GND), 5 / 6 AUX_12V.
Split termination, always fitted: 2 x 60.4R + 4.7 nF to LINK_GND (ADR 0006 decision 8).
ESD D13 at J15: Nexperia PESD2CANFD24V (24 V, 6 pF per line).
